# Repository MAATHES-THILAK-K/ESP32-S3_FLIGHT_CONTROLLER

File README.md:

# ESP32-S3 Flight Controller Board

A custom-designed flight controller based on the ESP32-S3 module, built for compatibility with the **esp-fc** firmware and **Betaflight-like** configuration.  
This board integrates essential flight-control sensors, power-management circuitry, and expansion interfaces, making it suitable for quadcopters, robotics, and experimental UAV platforms.

---

## 📌 Key Features

### **Core MCU**
- ESP32-S3 bare module
- Dual-core Xtensa LX7 processor
- Native USB for firmware flashing

### **Integrated Sensors**
- **MPU6050** – 6-axis gyro + accelerometer  
- **BMP180** – Barometric pressure & altitude sensor

### **Power System**
- **TP4056** Li-ion charging module with protection  
- **Boost converter (4.2 V → 5 V)** for stable ESP32-S3 power  
- On-board 3.3 V regulator

### **Motor & IO Support**
- **4-Motor outputs** (quad-rotor configuration)  
- Dedicated timer pins compatible with `esp-fc` firmware  
- JST-I2C connector for user-defined expansion modules

### **Firmware Compatibility**
- Fully compatible with  
  - https://github.com/rtlopez/esp-fc  
  - Betaflight-style configuration  
- Designed around the esp-fc recommended pin mappings

---

## 📂 Repository Structure

```

ESP32-FC-Board/
│
├── README.md              # Project documentation
├── LICENSE                # Apache license recommended
├── Hardware/
|___Gerber/                # Gerber files for PCB manufacturing
├── 3DModels/              # STEP/WRL models (optional)
└── Images/                # Photos, renders, pinout diagrams

```

---

## 🛠️ Hardware Overview

### **Sensors**
- MPU6050 connected via I2C  
- BMP180 connected via I2C  
- Pull-ups included where required  

### **Power Path**
- USB or battery input  
- Charging through TP4056  
- Protected 4.2 V → boosted 5 V  
- Local 3.3 V regulator for ESP32-S3 & sensors

### **Connectors**
- Motor outputs (4x)
- I2C JST connector for add-on modules
- Debug pads (TX/RX/5V/GND)

---

## 🚀 Firmware Setup

1. Clone the `esp-fc` firmware:  
```

[https://github.com/rtlopez/esp-fc](https://github.com/rtlopez/esp-fc)

```

2. Select **ESP32-S3 target** in configuration.

3. Flash firmware using:  
- Betaflight Configurator

4. Configure sensor orientation and motor mapping as per schematics.

---

## 📄 Manufacturing

The `Hardware/Gerber/` folder includes:
- Top/Bottom Copper  
- Solder mask  
- Silkscreen  
- Drill files  
- Board outline  

These files can be uploaded to any PCB manufacturer such as JLCPCB, PCBWay, or OSH Park.

---

## 📸 Images & Diagrams

Board renders, real PCB photos, and pin-mapping diagrams are available in:

[Images](Images)

---

## 📜 License

This project is open-source.  
Choose your preferred license (MIT recommended for hardware projects).

---

## 🙌 Contributions

Contributions, improvements, and documentation updates are welcome.  
Feel free to open issues or pull requests.

---

## 📧 Contact

For questions, improvements, or collaboration ideas, open an Issue or contact the project maintainer.

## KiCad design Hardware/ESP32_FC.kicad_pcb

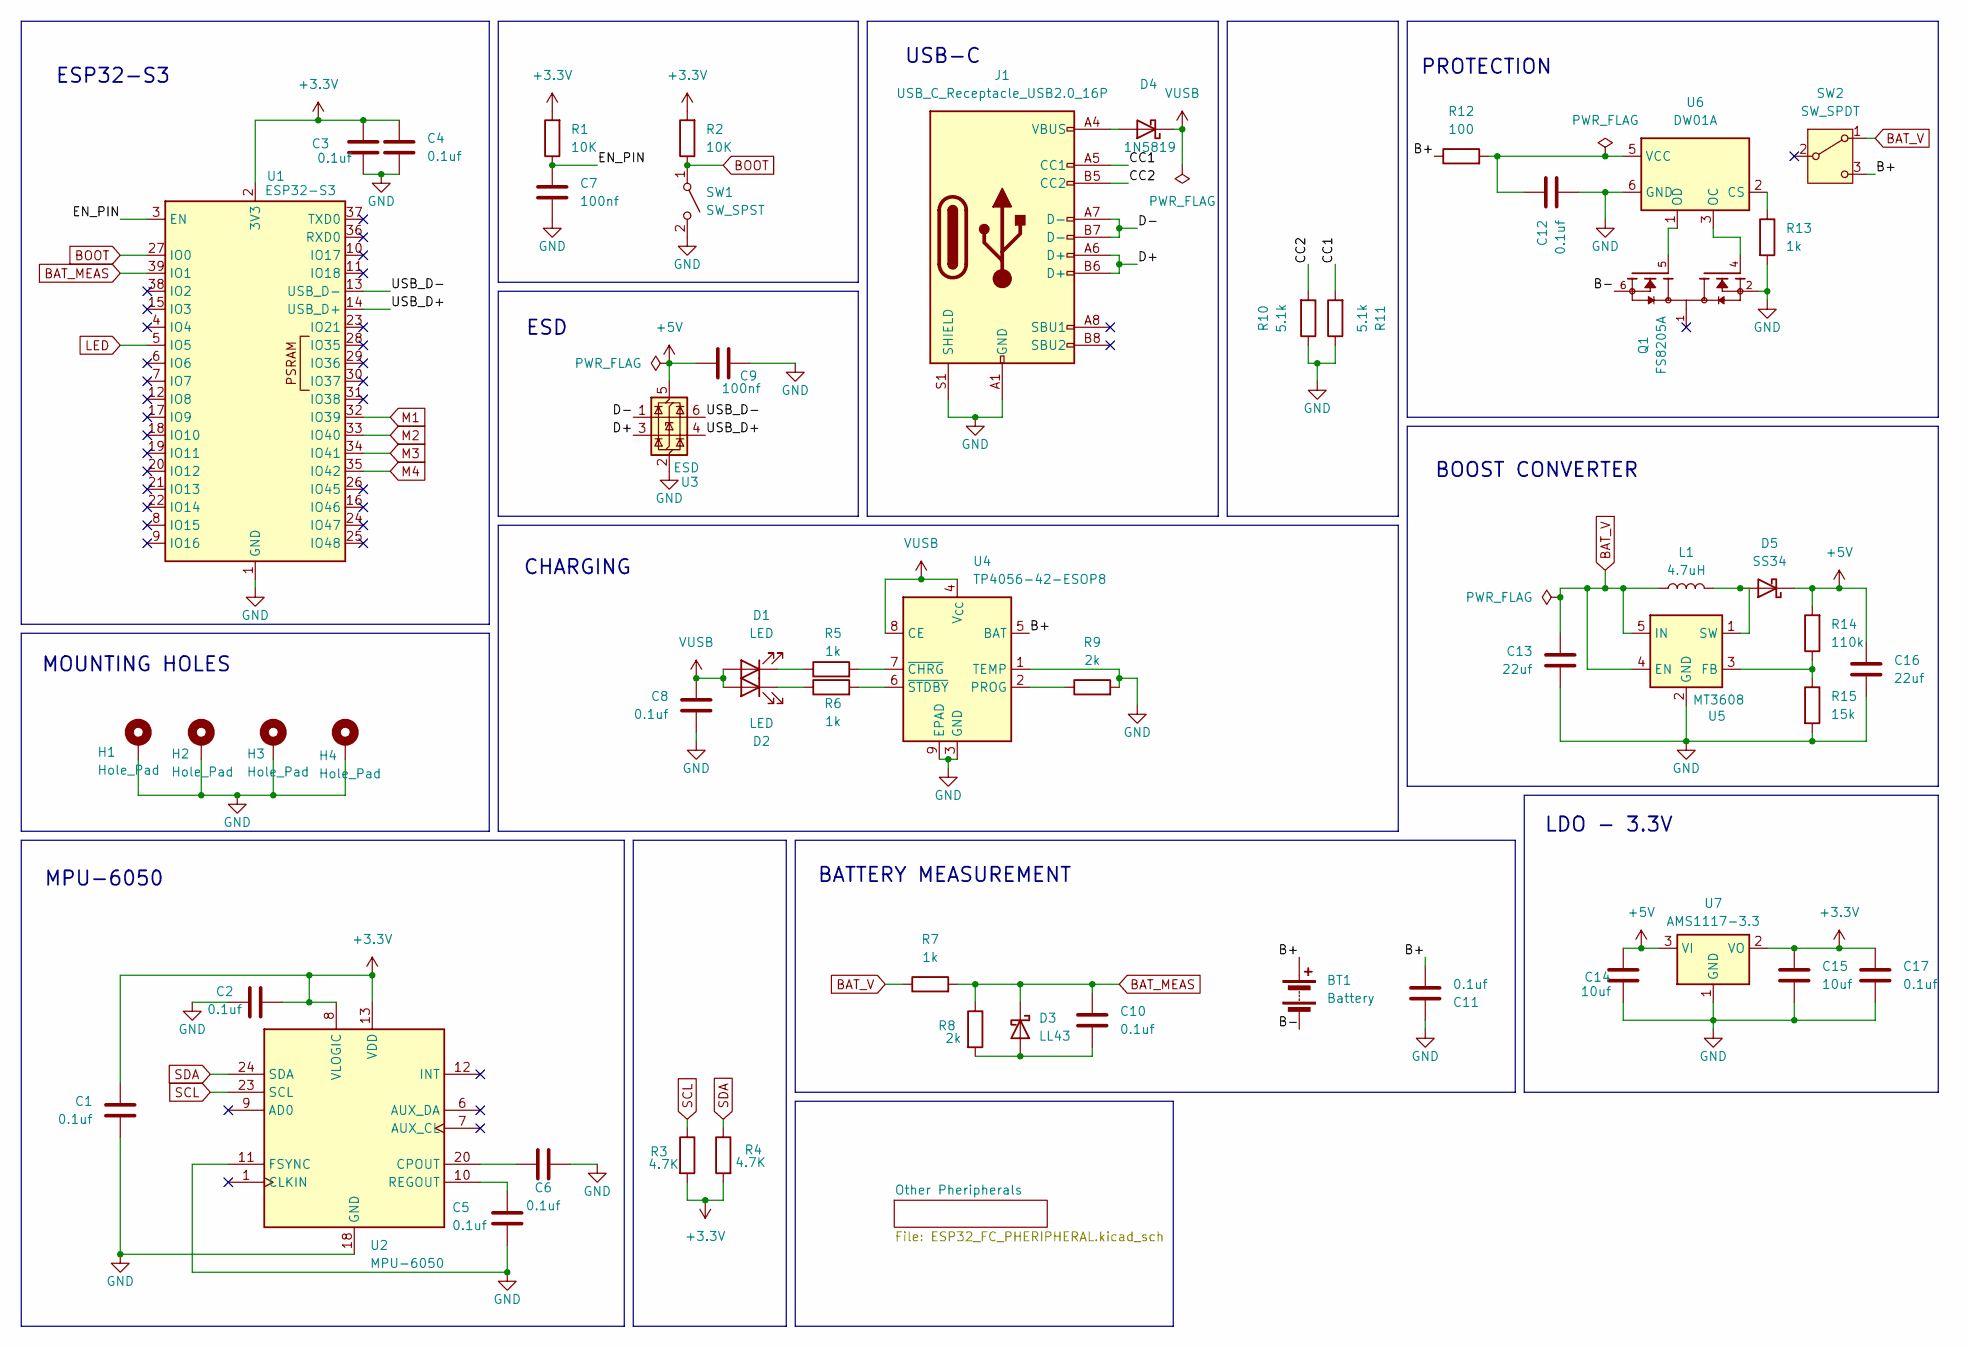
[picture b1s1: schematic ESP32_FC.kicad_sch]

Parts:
BT1: Battery; JST_PH_B2B-PH-K_1x02_P2.00mm_Vertical
C1, C2, C3, C4, C5, C6, C8, C10, C11, C12, C17: 0.1uf; C_0603_1608Metric
C7, C9: 100nf; C_0603_1608Metric
C13, C16: 22uf; C_0603_1608Metric
C14, C15: 10uf; C_0603_1608Metric
D1, D2: LED; LED_0805_2012Metric
D3: LL43; D_MiniMELF
D4: 1N5819; D_DO-41_SOD81_P10.16mm_Horizontal
D5: SS34; D_SMA
H1, H2, H3, H4: Hole_Pad; MountingHole_3.2mm_M3_Pad_Via
J1: USB_C_Receptacle_USB2.0_16P; USB_C_Receptacle_HRO_TYPE-C-31-M-12
L1: 4.7uH; C_0603_1608Metric
Q1: FS8205A; SOP65P640X120-8N; PARTREV 1.7
R1, R2: 10K; R_0603_1608Metric
R3, R4: 4.7K; R_0603_1608Metric
R5, R6, R7, R13: 1k; R_0603_1608Metric
R8, R9: 2k; R_0603_1608Metric
R10, R11: 5.1k; R_0603_1608Metric
R12: 100; R_0603_1608Metric
R14: 110k; R_0603_1608Metric
R15: 15k; R_0603_1608Metric
SW1: SW_SPST; SW_Tactile_SPST_NO_Straight_CK_PTS636Sx25SMTRLFS
SW2: SW_SPDT; SW_SPDT_PCM12
U1: ESP32-S3; ESP32-S3-WROOM-1
U2: MPU-6050; InvenSense_QFN-24_4x4mm_P0.5mm
U3: ESD; SOT-23-6
U4: TP4056-42-ESOP8; SOIC-8-1EP_3.9x4.9mm_P1.27mm_EP2.41x3.3mm_ThermalVias
U5: MT3608; SOT-23-6
U6: DW01A; SOT-23-6
U7: AMS1117-3.3; SOT-223-3_TabPin2

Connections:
+3.3V: C1.1, C2.2, C3.1, C4.1, C15.1, C17.1, R1.2, R2.2, R3.2, R4.2, U1.2 (3V3), U2.8 (VLOGIC), U2.13 (VDD), U7.2 (VO); also elsewhere on the board
+5V: C9.1, C14.1, C16.1, D5.1 (K), R14.2, U3.5 (VBUS), U7.3 (VI); also elsewhere on the board
/B+: BT1.1 (+), C11.2, R12.1, SW2.3 (C), U4.5 (BAT)
/B-: BT1.2 (-), Q1.6, Q1.7
/CC1: J1.A5 (CC1), R11.2
/CC2: J1.B5 (CC2), R10.2
/D+: J1.A6 (D+), J1.B6 (D+), U3.3 (I/O2)
/D-: J1.A7 (D-), J1.B7 (D-), U3.1 (I/O1)
/EN_PIN: C7.1, R1.1, U1.3 (EN)
/USB_D+: U1.14 (USB_D+), U3.4 (I/O2)
/USB_D-: U1.13 (USB_D-), U3.6 (I/O1)
BAT_MEAS: C10.1, D3.1 (K), R7.2, R8.1, U1.39 (IO1)
BAT_V: C13.1, L1.1, R7.1, SW2.1 (A), U5.4 (EN), U5.5 (IN)
BOOT: R2.1, SW1.1 (A), U1.27 (IO0)
GND: C1.2, C2.1, C3.2, C4.2, C5.2, C6.2, C7.2, C8.2, C9.2, C11.1, C12.2, C13.2, C14.2, C15.2, C16.2, C17.2, H1.1, H2.1, H3.1, H4.1, J1.A1 (GND), J1.A12 (GND), J1.B1 (GND), J1.B12 (GND), J1.S1 (SHIELD), Q1.2, Q1.3, R9.2, R10.1, R11.1, R13.2, R15.2, SW1.2 (B), U1.1 (GND), U1.40 (GND), U1.41 (GND), U2.11 (FSYNC), U2.18 (GND), U3.2 (GND), U4.1 (TEMP), U4.3 (GND), U4.9 (EPAD), U5.2 (GND), U6.6 (GND), U7.1 (GND); also elsewhere on the board
LED: U1.5 (IO5); also elsewhere on the board
M1: U1.32 (IO39); also elsewhere on the board
M2: U1.33 (IO40); also elsewhere on the board
M3: U1.34 (IO41); also elsewhere on the board
M4: U1.35 (IO42); also elsewhere on the board
unnamed: D1.1 (K), R5.1
unnamed: D2.1 (K), R6.1
unnamed: C10.2, D3.2 (A), R8.2
unnamed: D4.2 (A), J1.A4 (VBUS), J1.A9 (VBUS), J1.B4 (VBUS), J1.B9 (VBUS)
unnamed: D5.2 (A), L1.2, U5.1 (SW)
unnamed: C6.1, U2.20 (CPOUT)
unnamed: C5.1, U2.10 (REGOUT)
unnamed: R9.1, U4.2 (PROG)
unnamed: R5.2, U4.7 (~CHRG)
unnamed: R6.2, U4.6 (~STDBY)
unnamed: R14.1, R15.1, U5.3 (FB)
unnamed: R13.1, U6.2 (CS)
unnamed: Q1.4, U6.3 (OC)
unnamed: Q1.5, U6.1 (OD)
unnamed: C12.1, R12.2, U6.5 (VCC)
SCL: R3.1, U2.23 (SCL); also elsewhere on the board
SDA: R4.1, U2.24 (SDA); also elsewhere on the board
VUSB: C8.1, D1.2 (A), D2.2 (A), D4.1 (K), U4.4 (V_{CC}), U4.8 (CE)

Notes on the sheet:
PROTECTION
CHARGING
ESP32-S3
BOOST CONVERTER
ESD
MOUNTING HOLES
BATTERY MEASUREMENT
USB-C
LDO - 3.3V
MPU-6050

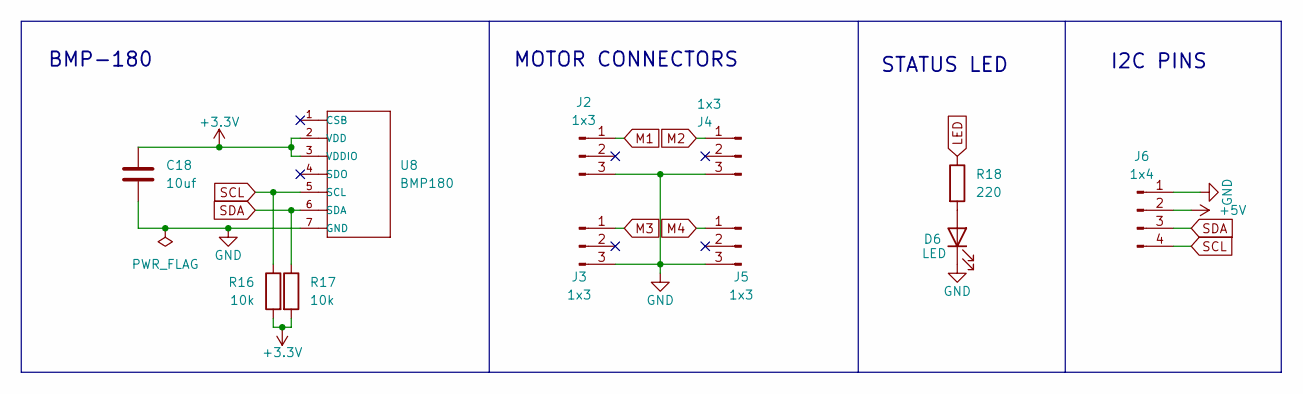
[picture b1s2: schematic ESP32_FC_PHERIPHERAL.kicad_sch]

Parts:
C18: 10uf; C_0603_1608Metric
D6: LED; LED_0805_2012Metric
J2, J3, J4, J5: 1x3; PinHeader_1x03_P2.54mm_Vertical
J6: 1x4; JST_PH_B4B-PH-K_1x04_P2.00mm_Vertical
R16, R17: 10k; R_0603_1608Metric
R18: 220; R_0603_1608Metric
U8: BMP180; LGA7-1.5-3.8X3.6MM; MPN BMP18

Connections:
+3.3V: C18.1, R16.2, R17.2, U8.2 (VDD), U8.3 (VDDIO); also elsewhere on the board
+5V: J6.2; also elsewhere on the board
GND: C18.2, D6.1 (K), J2.3, J3.3, J4.3, J5.3, J6.1, U8.7 (GND); also elsewhere on the board
LED: R18.1; also elsewhere on the board
M1: J2.1; also elsewhere on the board
M2: J4.1; also elsewhere on the board
M3: J3.1; also elsewhere on the board
M4: J5.1; also elsewhere on the board
unnamed: D6.2 (A), R18.2
SCL: J6.4, R16.1, U8.5 (SCL); also elsewhere on the board
SDA: J6.3, R17.1, U8.6 (SDA); also elsewhere on the board

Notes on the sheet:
MOTOR CONNECTORS
I2C PINS
BMP-180
STATUS LED

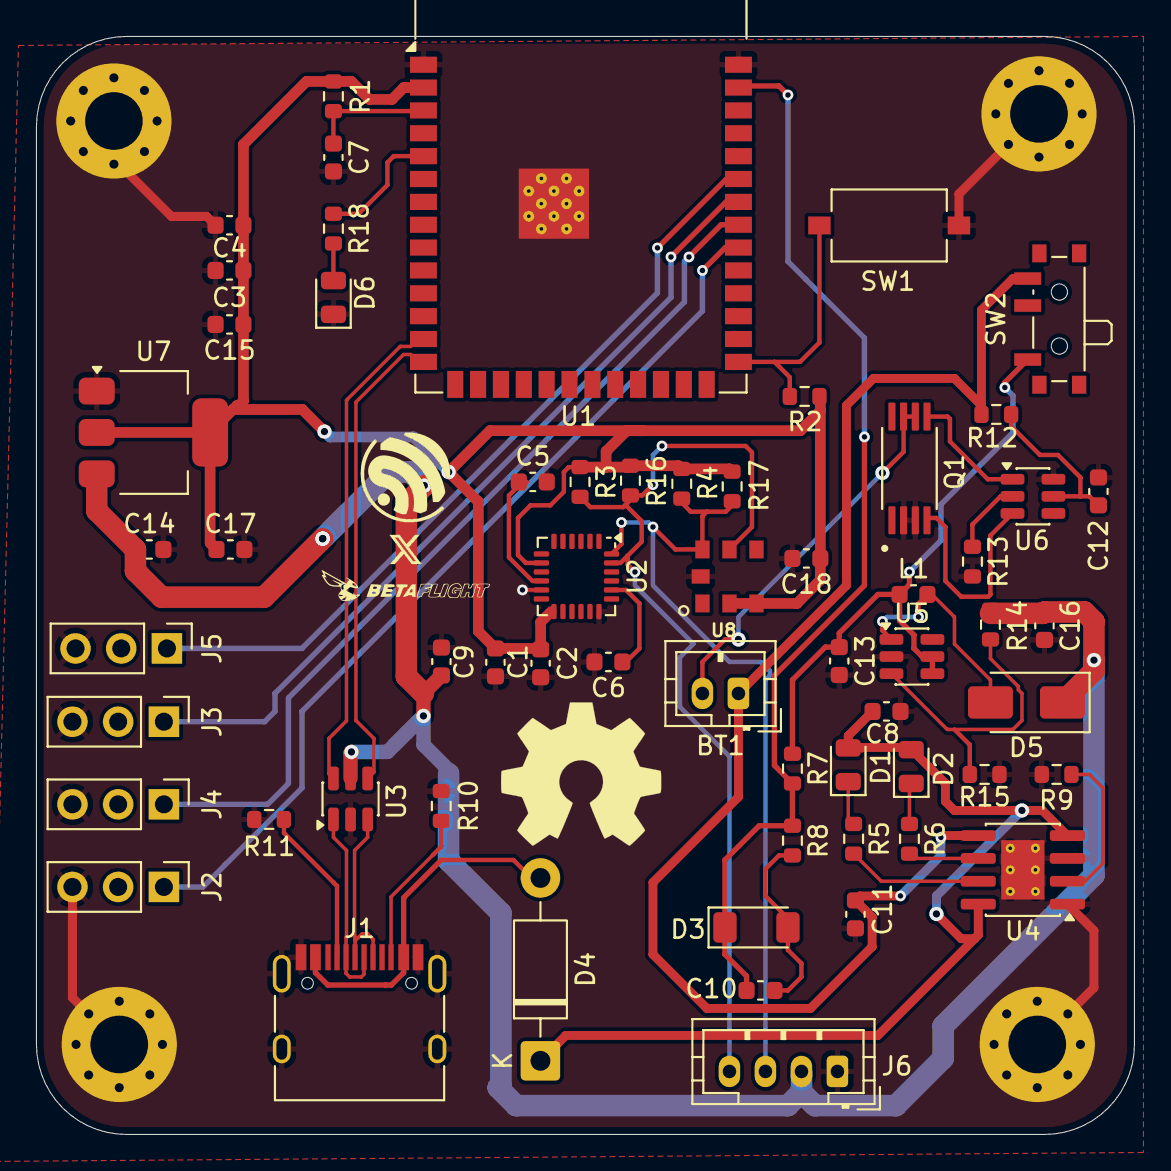
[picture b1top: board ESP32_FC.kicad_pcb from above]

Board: 2 copper layers, 61.0 x 61.0 mm, 65 parts (0 on the bottom side), 39 nets.

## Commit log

2025-12-08 Create temp
